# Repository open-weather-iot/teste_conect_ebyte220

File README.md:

# teste_conect_ebyte220
Neste repositório será armazenado os códigos para teste de cobertura rádio utilizando o módulo E220 do fabricante Ebyte

As bibliotecas utilizadas foram:
RP2040_SD para o cartão de memória, Ebyte para o módulo LoRa E220, Tiny GPS para o módulo GPS, Adafruit GFX e Adafruit SSD1306 para o display oled 
SPI.

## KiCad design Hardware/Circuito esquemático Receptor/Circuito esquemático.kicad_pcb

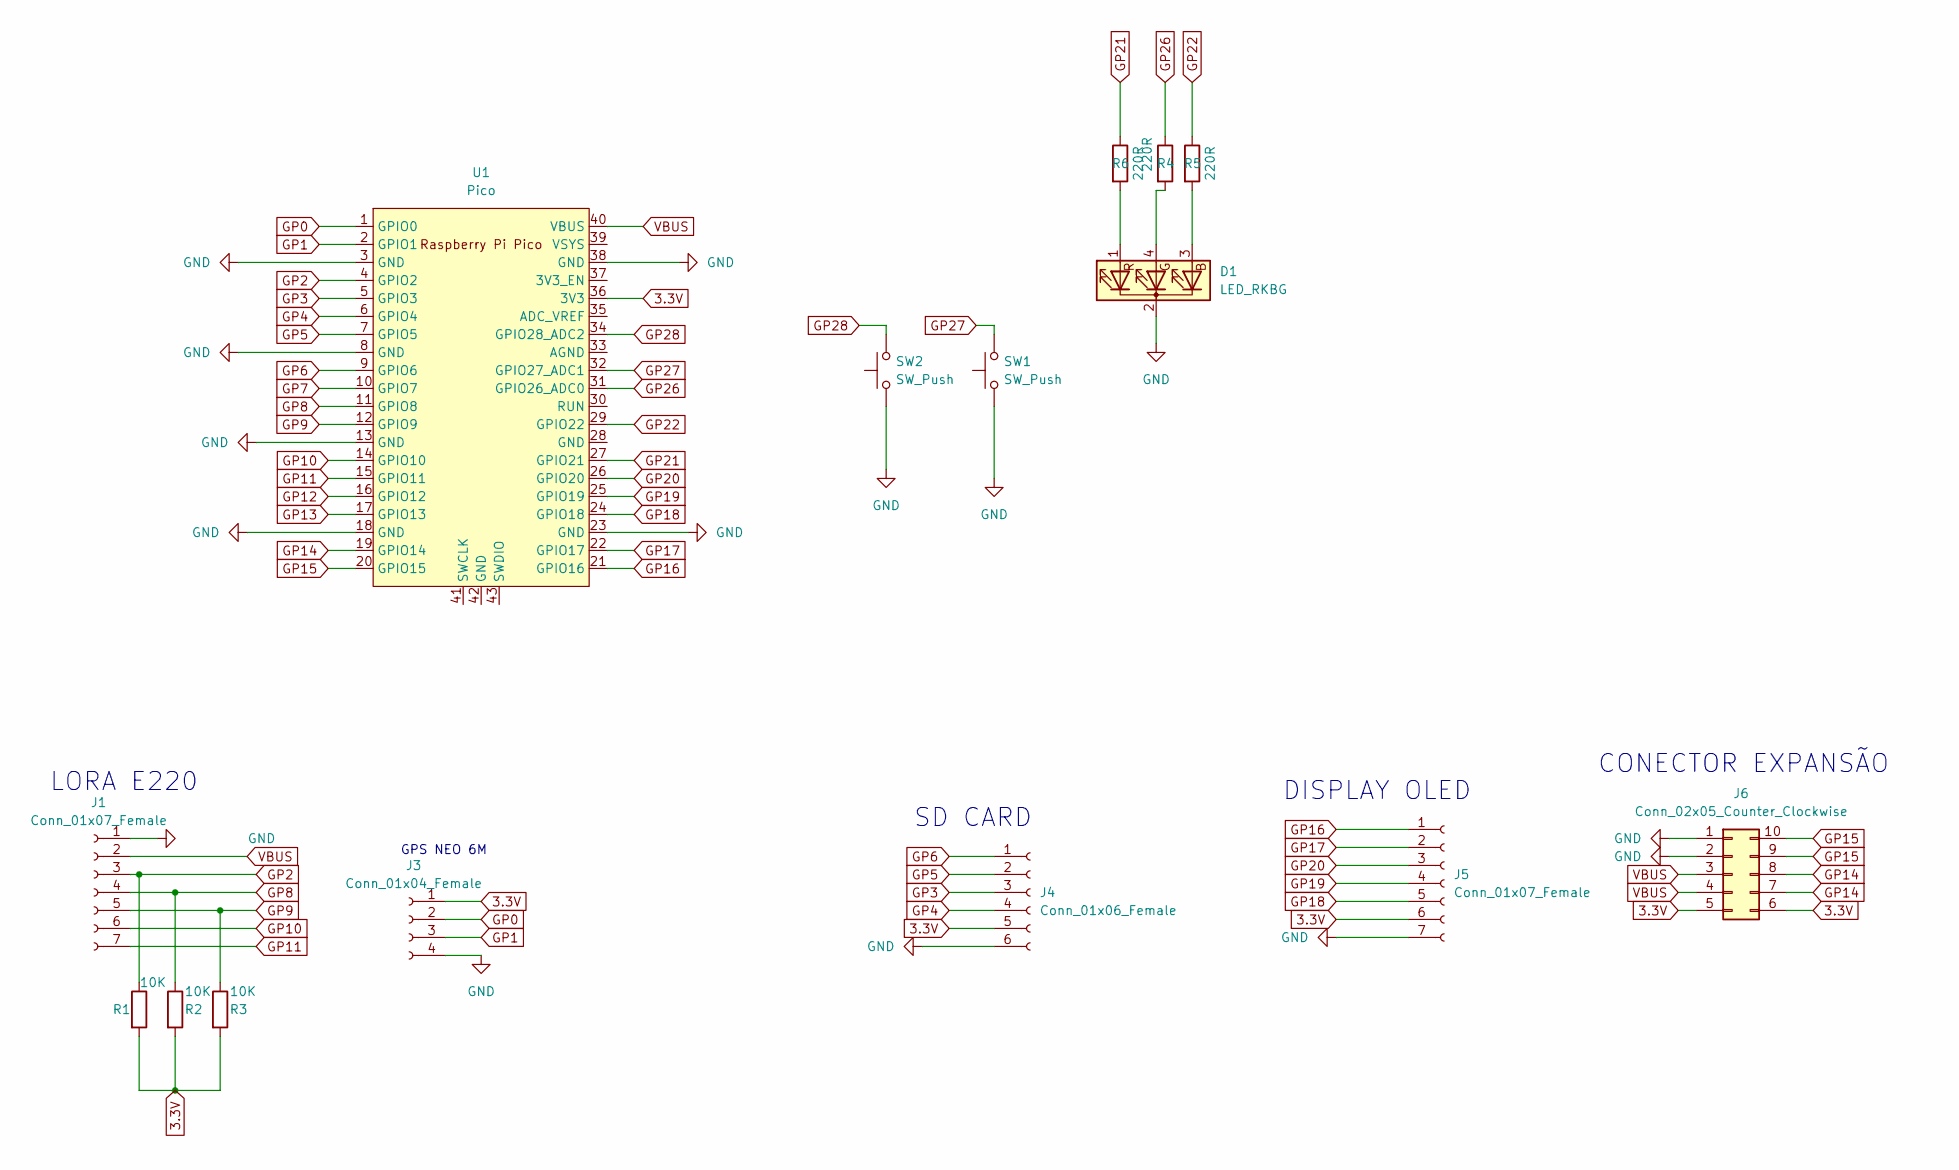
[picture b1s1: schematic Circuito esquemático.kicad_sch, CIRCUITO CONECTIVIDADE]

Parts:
D1: LED_RKBG; LED_D5.0mm-4_RGB
J1, J5: Conn_01x07_Female; PinSocket_1x07_P2.54mm_Vertical
J3: Conn_01x04_Female; PinSocket_1x04_P2.54mm_Vertical
J4: Conn_01x06_Female; PinSocket_1x06_P2.54mm_Horizontal
J6: Conn_02x05_Counter_Clockwise; IDC-Header_2x05_P2.54mm_Vertical
R1, R2, R3: 10K; R_Axial_DIN0207_L6.3mm_D2.5mm_P10.16mm_Horizontal
R4, R5, R6: 220R; R_Axial_DIN0207_L6.3mm_D2.5mm_P10.16mm_Horizontal
SW1, SW2: SW_Push; SW_PUSH_6mm
U1: Pico; RPi_Pico_SMD_TH

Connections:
3.3V: J3.1, J4.5, J5.6, J6.5, J6.6, R1.2, R2.2, R3.2, U1.36 (3V3)
GND: D1.2 (K), J1.1, J3.4, J4.6, J5.7, J6.1, J6.2, SW1.1, SW2.1, U1.3 (GND), U1.8 (GND), U1.13 (GND), U1.18 (GND), U1.23 (GND), U1.38 (GND)
GP0: J3.2, U1.1 (GPIO0)
GP1: J3.3, U1.2 (GPIO1)
GP2: J1.3, R1.1, U1.4 (GPIO2)
GP3: J4.3, U1.5 (GPIO3)
GP4: J4.4, U1.6 (GPIO4)
GP5: J4.2, U1.7 (GPIO5)
GP6: J4.1, U1.9 (GPIO6)
GP7: U1.10 (GPIO7)
GP8: J1.4, R2.1, U1.11 (GPIO8)
GP9: J1.5, R3.1, U1.12 (GPIO9)
GP10: J1.6, U1.14 (GPIO10)
GP11: J1.7, U1.15 (GPIO11)
GP12: U1.16 (GPIO12)
GP13: U1.17 (GPIO13)
GP14: J6.7, J6.8, U1.19 (GPIO14)
GP15: J6.9, J6.10, U1.20 (GPIO15)
GP16: J5.1, U1.21 (GPIO16)
GP17: J5.2, U1.22 (GPIO17)
GP18: J5.5, U1.24 (GPIO18)
GP19: J5.4, U1.25 (GPIO19)
GP20: J5.3, U1.26 (GPIO20)
GP21: R6.1, U1.27 (GPIO21)
GP22: R5.1, U1.29 (GPIO22)
GP26: R4.1, U1.31 (GPIO26_ADC0)
GP27: SW1.2, U1.32 (GPIO27_ADC1)
GP28: SW2.2, U1.34 (GPIO28_ADC2)
unnamed: D1.1 (RA), R6.2
unnamed: D1.3 (BA), R5.2
unnamed: D1.4 (GA), R4.2
VBUS: J1.2, J6.3, J6.4, U1.40 (VBUS)

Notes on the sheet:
CONECTOR EXPANSÃO
GPS NEO 6M
DISPLAY OLED
LORA E220
SD CARD

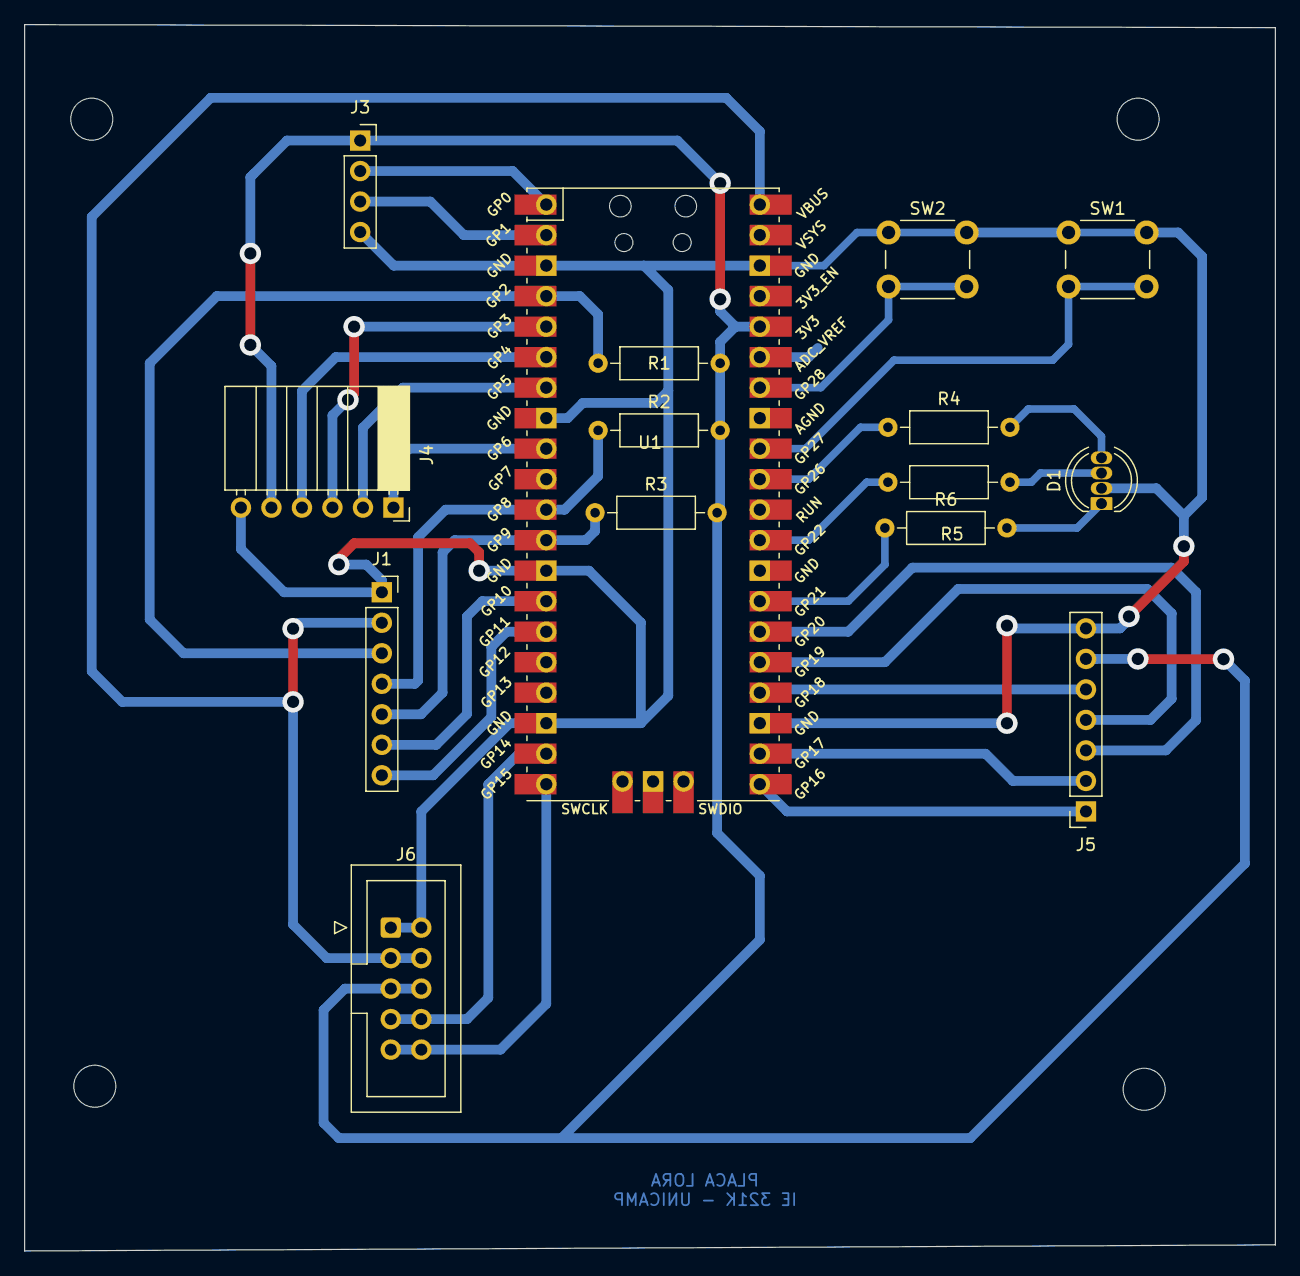
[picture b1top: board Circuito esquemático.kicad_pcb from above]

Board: 2 copper layers, 104.1 x 102.1 mm, 15 parts (0 on the bottom side), 29 nets.

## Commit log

2022-12-13 firmware test module Ebyte
2022-12-14 library card sd with Raspberry Pico
2022-12-14 library module E220
2022-12-14 firmware LoRa transmiter
2022-12-14 Update README.md
    Atualização da descrição do repositório
2022-12-14 Projeto de hardware das placas de conectividade modulo Ebyte 220
